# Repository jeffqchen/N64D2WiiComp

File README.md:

# N64D2WiiComp

A dongle for connecting a Wii component video cable to a N64Digital modded Nintendo 64

-----------

This adapter allows you to plug a Wii video cable into the AV Multi port into an Nintendo 64. The primary purpose is to allow the use of Wii component video cable on Nintendo 64 consoles modded with N64Digital and UltraHDMI in YUV mode.

## N64Digital Dual Output

You can use this adapter in combination with my mini to full HDMI dongle to achive dual output. Details:
https://www.thingiverse.com/thing:4924766

## Variation

### [N64D2VGA](../../../SNES2VGA/tree/main/N64D2VGA)

Output analogue RGBS video and digital HDMI signal at the same time.

-----------

## Part

- 3D Printed shell (also available on GitHub) - [Link](https://www.thingiverse.com/thing:4945082)

- PCB (also available on GitHub)
  - [Main](https://oshpark.com/shared_projects/ULsxf6av)
  - [Sub](https://oshpark.com/shared_projects/Sx7UN638)

- Nintendo Video Plug - [Link](https://github.com/jeffqchen/JeffParts/blob/main/Connectors/Nintendo%20AV%20Plug/info.md)

- M2x12mm (total length 13.8mm) screw and hex nut - [Link](https://github.com/jeffqchen/JeffParts/blob/main/Parts/M2%20M3%20Hex%20Screw%20%26%20Nut/info.md)

-----------

## 3D Print

Print the parts upside down for accurate port dimensions.
If you prefer better exterior look, print upright with a raft to minimize height error.

The ring is for joining this adapter together with the mini HDMI to full HDMI adapter for the N64Digital, for better mechanical rigidity. It should also help even if the HDMI adapter is not in place, so the adapter can't sag and damage anything.
https://www.thingiverse.com/thing:4924766

-----------
## Before Assembly

File the Wii end of the PCB that goes into the component cable, so it has a chamfer on both the top and bottom side of the board. This is to ensure it doesn't damage or destroy the contacts inside your Wii component cable.

Please note the white line near the end of the golden fingers. It is recommended you file the edge all the way down to the line at 45 degrees.

-----------

## Assembly

Solder the two PCBs toghether. Note the "This should NOT be visible" silkscreen print and obey. Then solder the SNES header onto the PCB assembly. Note the "Top" print. This indicates the way the notch on the plug should face.

Place the soldered assembly into the printed shell and screw them together.

----------
## Misc

The composite signal is also connected by default. You can use a composite video cable for the Wii for composite video output.

It is possible to sever the default jumper on the PCB and then bridge Luma or CSync for connecting an RGBs cable. However there will be extra components required for such cable to function properly.

----------
## Special Thanks
Rainy Day Retro, the one who requested this to be made
- https://twitter.com/rainydayretro

citrus3000psi, the super famous creator of many console mods
- https://twitter.com/citrus3000psi
- https://www.black-dog.tech

qwertymodo
- https://twitter.com/qwertymodo

Shank
- https://twitter.com/ShankMods

----------
Shield: [![CC BY-SA 4.0][cc-by-sa-shield]][cc-by-sa]

This work is licensed under a
[Creative Commons Attribution-ShareAlike 4.0 International License][cc-by-sa].

[![CC BY-SA 4.0][cc-by-sa-image]][cc-by-sa]

[cc-by-sa]: http://creativecommons.org/licenses/by-sa/4.0/
[cc-by-sa-image]: https://licensebuttons.net/l/by-sa/4.0/88x31.png
[cc-by-sa-shield]: https://img.shields.io/badge/License-CC%20BY--SA%204.0-lightgrey.svg

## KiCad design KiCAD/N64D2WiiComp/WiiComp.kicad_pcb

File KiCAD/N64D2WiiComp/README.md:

# N64D2WiiComp
A dongle for connecting a Wii component video cable to a N64Digital modded Nintendo 64

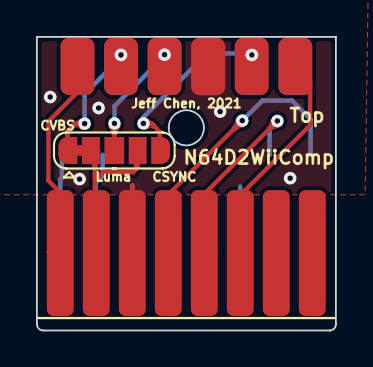
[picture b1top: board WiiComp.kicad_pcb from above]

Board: 2 copper layers, 16.6 x 16.3 mm, 4 parts (0 on the bottom side), 11 nets.

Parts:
JP1: CVBS/Luma Jumper; SolderJumper-3_P1.3mm_Bridged12_RoundedPad1.0x1.5mm
JP2: CSync/Luma Jumper; SolderJumper-3_P1.3mm_Open_RoundedPad1.0x1.5mm
P1: AVMulti_Main; AV_Multi_Main
P2: Wii_AV_Multi

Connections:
/+5V: P1.10, P2.4
/Audio_L: P1.11, P2.1
/Audio_R: P1.12, P2.2
/CSync: JP2.1, P1.3
/CVBS: JP1.1, P1.9
/Luma: JP1.3, JP2.3, P1.7
/Pb: P1.4, P2.9
/Pr: P1.1, P2.11
/Sync: JP1.2, JP2.2, P2.3
/Y: P1.2, P2.7
GND: P1.5, P1.6, P2.5, P2.6, P2.12

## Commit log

2021-09-23 Initial upload
2021-09-23 Fix files
2021-09-23 Upload pictures
2021-09-23 Adjust readme
2021-09-23 Add filing details
2021-09-23 Add sync info
2021-09-23 Fix readme formatting
2021-10-24 Update PCB
2022-08-09 Change license type
